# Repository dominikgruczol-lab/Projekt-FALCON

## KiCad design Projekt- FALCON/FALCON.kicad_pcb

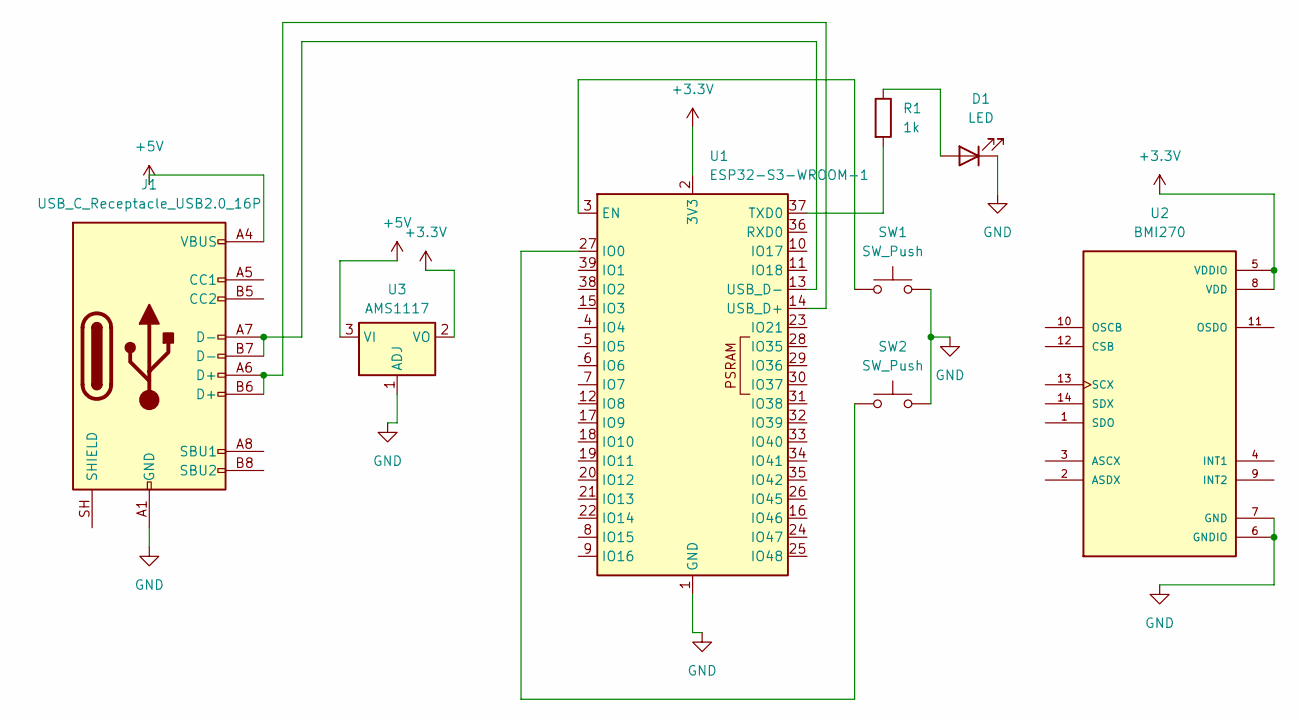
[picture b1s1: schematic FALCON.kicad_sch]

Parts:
D1: LED; LED_0805_2012Metric
J1: USB_C_Receptacle_USB2.0_16P; USB_C_Receptacle_HRO_TYPE-C-31-M-12
R1: 1k; R_0805_2012Metric
SW1, SW2: SW_Push; SW_SPST_PTS645Sx43SMTR92
U1: ESP32-S3-WROOM-1
U2: BMI270; XDCR_BMI270
U3: AMS1117; SOT-223-3_TabPin2

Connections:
+3.3V: U1.2 (3V3), U2.5 (VDDIO), U2.8 (VDD), U3.2 (VO)
+5V: J1.A4 (VBUS), J1.A9 (VBUS), J1.B4 (VBUS), J1.B9 (VBUS), U3.3 (VI)
GND: D1.1 (K), J1.A1 (GND), J1.A12 (GND), J1.B1 (GND), J1.B12 (GND), SW1.2, SW2.2, U1.1 (GND), U1.40 (GND), U1.41 (GND), U2.6 (GNDIO), U2.7 (GND), U3.1 (ADJ)
unnamed: D1.2 (A), R1.1
unnamed: SW1.1, U1.3 (EN)
unnamed: SW2.1, U1.27 (IO0)
unnamed: R1.2, U1.37 (TXD0)
unnamed: J1.A6 (D+), J1.B6 (D+), U1.14 (USB_D+)
unnamed: J1.A7 (D-), J1.B7 (D-), U1.13 (USB_D-)

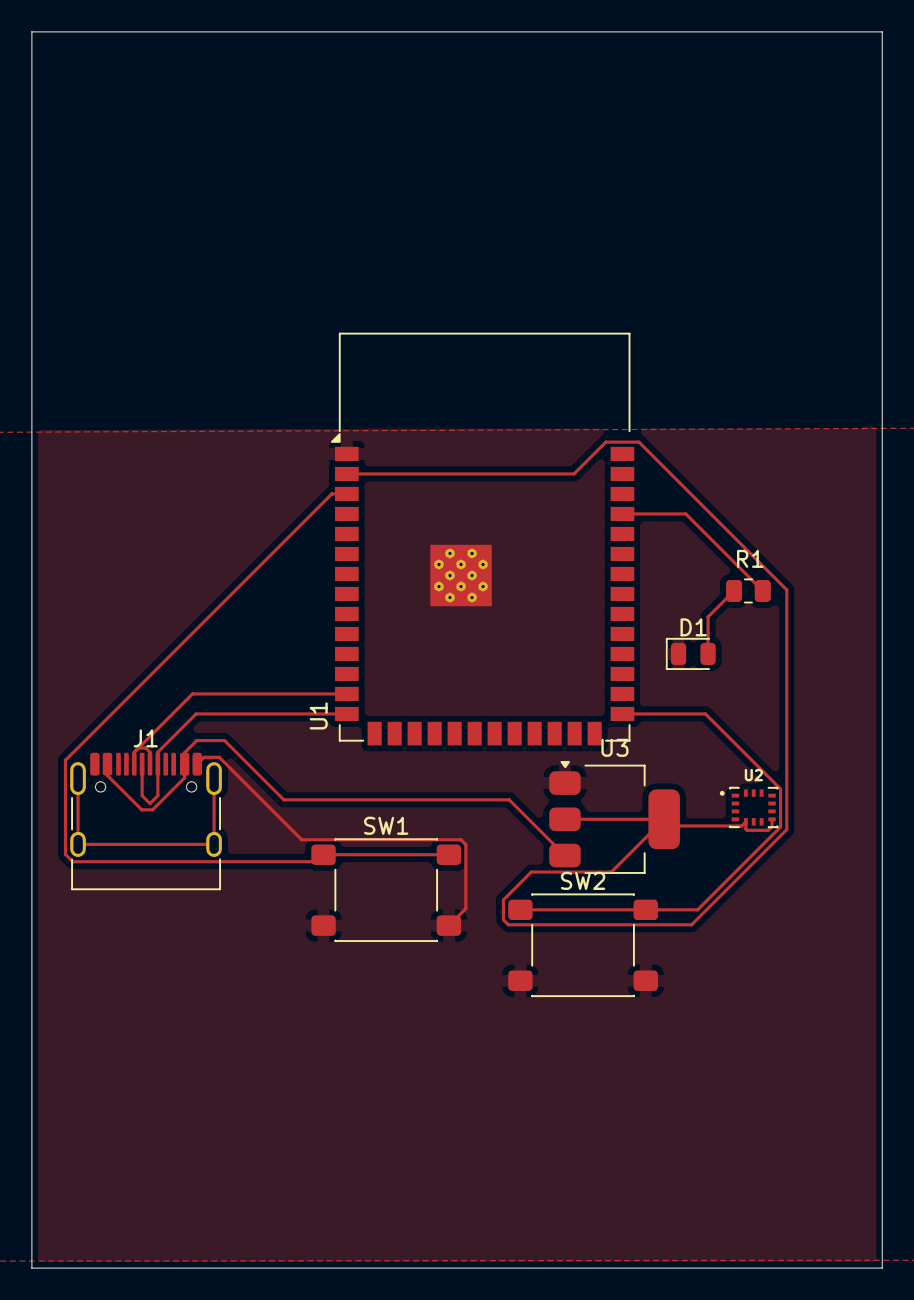
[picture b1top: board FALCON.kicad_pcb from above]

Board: 2 copper layers, 54.0 x 78.5 mm, 8 parts (0 on the bottom side), 9 nets.

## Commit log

2026-03-25 Projekt- FALCON
